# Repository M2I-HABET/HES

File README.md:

# HES Revision 5.0
Repository for the HABET Engineering System (HES). The HES system is the engineering hardware
system used by the HABET team for all spacecraft. This includes the base electronics, software,
enclosure, and any support hardware used for any HABET flight. Originally, this only included the 
base electronics used. In 2020, this was expanded to include all engineering systems in HABET and
rolled out as HES 4.0. 

This repo serves as a central hub for managing the systems and has submodules for additional 
GitHub repos used that make up the HES family of hardware/software. These repos currently include

- HAR (High Altitude Reporter) - Main on-board computer and tracking system
- BERT (Back Emergency Recovery Transmitter) - Backup tracking system using a SatComm relay
- THOR (The High-voltage Output Regulator) - Main power distribution board
- ATHENA (Advanced Telemetry and High-Alitude Environmental Networking Assistant) - Payload computer system
- Gemini - Cube-shaped spacecraft with shelves used to divide different functional bays
- Apollo - Puck design to create a cylinder spacecraft with each puck containing hardware/payloads.

Others may be added as needed.

HES 5.0 will have the following features:

* Standardized to the PCIe 1x connector for interconnection. Backplane for Gemini and PCIe extension cables for Apollo
* Custom Power Management Module (THOR) to manage power to all sub-systems
* Support for QWICC connectors (I2C) for additional sensors through HAR and BERT
* Moved to the M.2 connectors and the SparkFun MicroMod board.
* Move to 3D printable enclosures for both Gemini and Apollo
* Front panel support for external power, switching on and off, and status lights
* 915 LoRa system for TT&C (Telemetry, Tracking & Control), 433 MHz LoRa for Payload 

Future support will include:
* Support for WiFi features using the ESP32 board on HAR
* POE Power management for WiFi adapters (Rocket M5)

POE support is a long-term goal as we have moved away from POE devices, but it would be useful in future missions. A shorter term goal is to utilize the ESP32 to provide real-time feedback for testing and pre-launch setup of the spacecraft.

More information can be found in our Wiki.

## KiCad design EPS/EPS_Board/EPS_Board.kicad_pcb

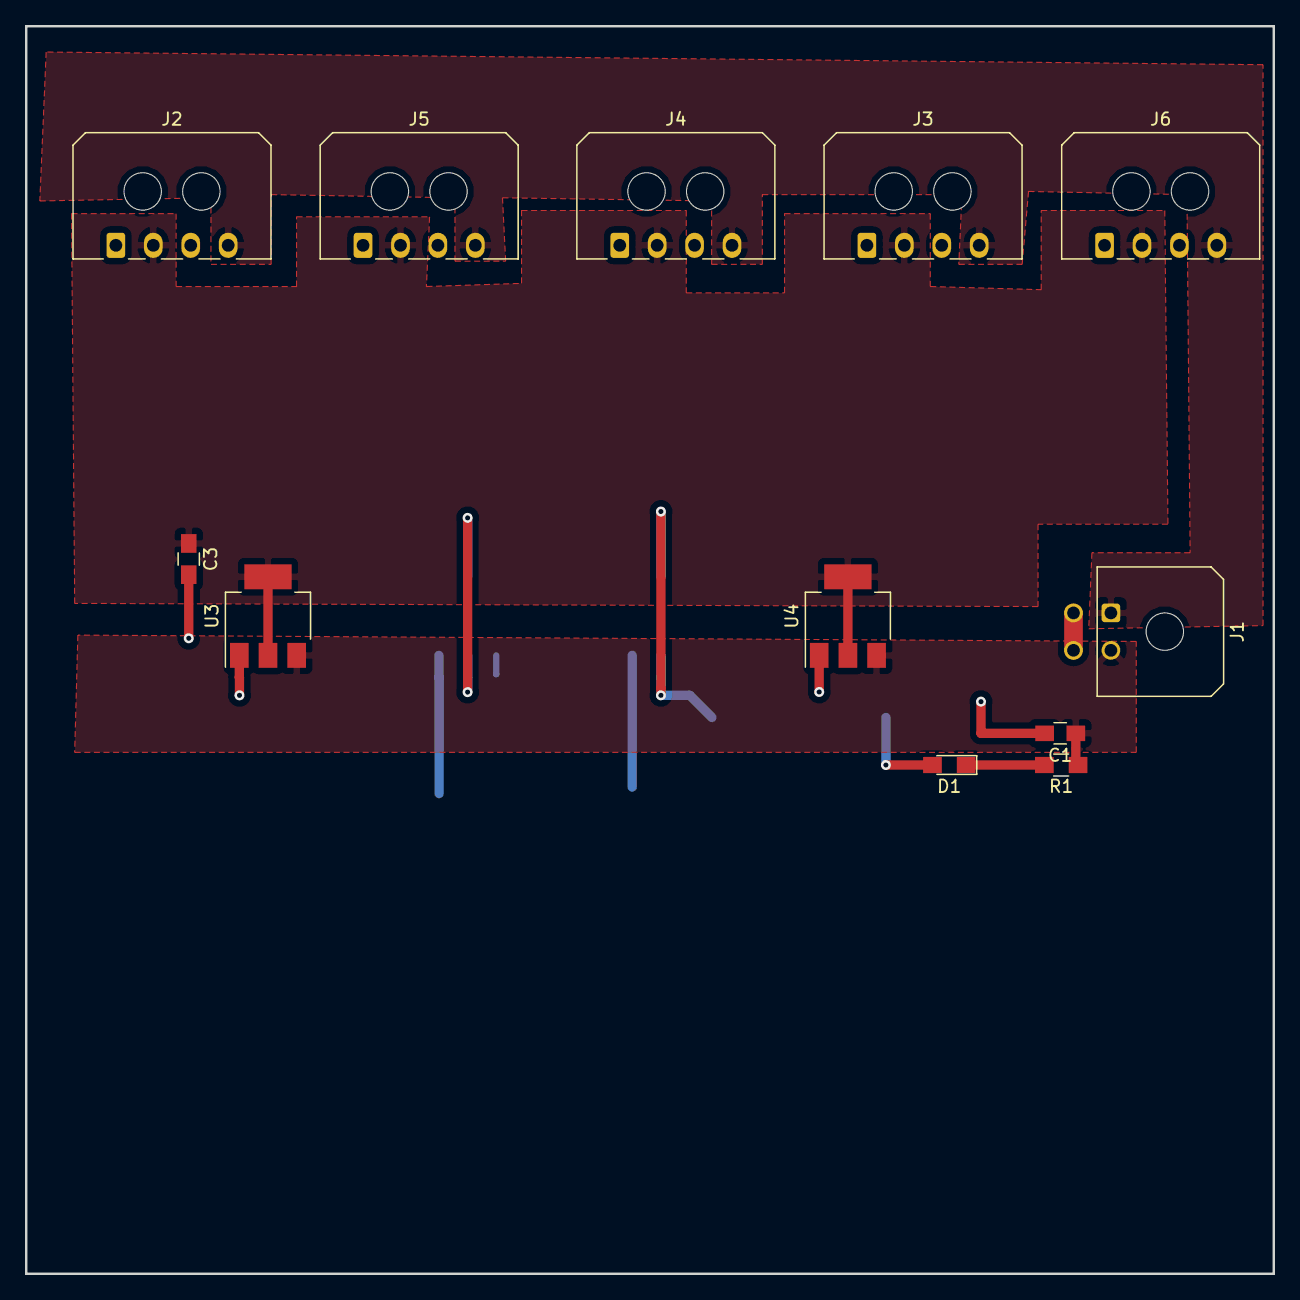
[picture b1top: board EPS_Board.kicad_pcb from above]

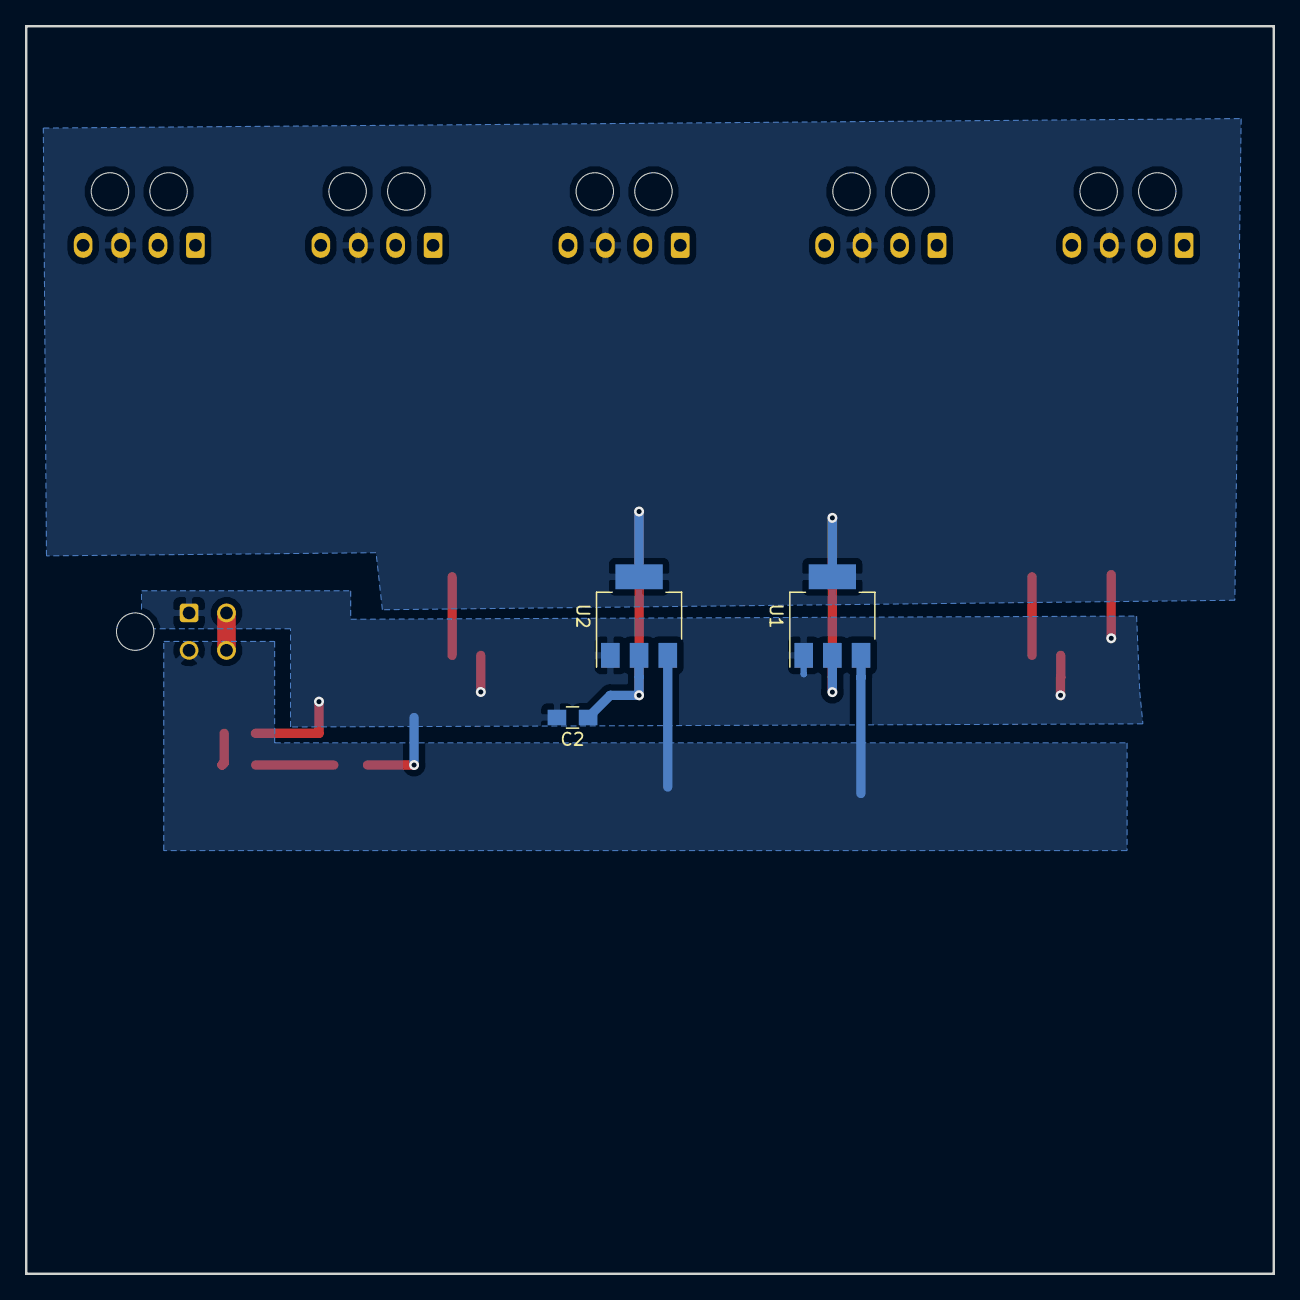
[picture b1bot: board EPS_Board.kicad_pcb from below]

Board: 2 copper layers, 100.0 x 100.0 mm, 15 parts (3 on the bottom side), 6 nets.

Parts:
C1, C2, C3: CAP; C_0805_HandSoldering
D1: LED; LED_0805_HandSoldering
J1: Conn_02x02_Counter_Clockwise; Molex_Micro-Fit_3.0_43045-0400_2x02_P3.00mm_Horizontal
J2, J3, J4, J5, J6: Conn_01x04_Female; Molex_Micro-Fit_3.0_43650-0400_1x04_P3.00mm_Horizontal
R1: R; R_0805_HandSoldering
U1, U2: AZ1117-3.3; SOT-223-3_TabPin2
U3, U4: AZ1117-5.0; SOT-223-3_TabPin2

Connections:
+3V3: C2.1, J2.3, J3.3, J4.3, J5.3, J6.3, U1.2, U2.2
+5V: C3.1, J2.2, J3.2, J4.2, J5.2, J6.2, U3.2, U4.2
+BATT: C1.1, J1.2, R1.1, U1.3, U2.3, U3.3, U4.3
GND: C1.2, C2.2, C3.2, D1.2, J1.1, J2.4, J3.4, J4.4, J5.4, J6.4, U1.1, U2.1, U3.1, U4.1
unnamed: D1.1, R1.2
unnamed: J1.3, J1.4

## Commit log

2019-01-02 Adding rev 1 of the board. Basic as heck.
2019-01-02 Added caps for the lin regs. also added a led for coolnessss.
2019-01-02 fixed pad spacing
2019-01-08 Updated for individual caps for the linear regs.
2019-07-03 Create fp-info-cache
2020-12-21 Update README.md
    Update to readme
2020-12-22 Update README.md
    Re-Write based on recent meeting and discussion.
2021-01-06 Moved old work to different directory, put new board schematic in its place
2021-04-09 New software for BERT 3.0
2021-04-11 BERTV3 is working for now albeit without printing to a file...
2021-04-11 Seems to be working but I can't read the file that was created...
2021-04-11 not done yet
2021-04-11 Updated file, at a working state
    Datalogging working, environmental sensors working, GPS working. Displays to both serial and display.
2021-04-22 Update for SatCom
2021-04-29 Update BERTV3.ino
    Working copy. Many things are JAF. Will re-write later. But this does work with SatComm and data storage
2021-05-12 Start on new PCB
2021-06-22 Update BERTV3.ino
    Minor fix to reduce packet size
2021-06-23 Update BERTV3.ino
    Second revision to reduce packet size
2021-07-03 Update README.md
    Revised to reflect some changes in the HABET repos
2021-07-19 Update README.md
    Clarified some things
2026-02-03 Revise README for HES Revision 5.0
    Updated README to reflect changes from HES 4.0 to HES 5.0, including new features and corrections.
